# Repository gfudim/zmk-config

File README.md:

# zmk-config

## shallow miryoku zmk-config repo

A shallow "miryoku" layout implementation for my 36-Keys, diode-free/gpio-direct, custom keyboard.

### Parts

* PCB - 2 PCBs of K-36 split keyboard
* Controller - 2 Nice Nano micro controller
* Switches - 36 Kailh Choc switches of your choice
* Sockets - 36 Kailh hotswap sockets for choc switches
* Keycaps - 34 Choc keycaps, 2 Choc homing keycaps
* On\Off Switch - 2 PCM12SMTR micro toggle switch
* Reset Button - 2 B3U-1000P MD 2-foot tact switch 3*2.5*1.6 Micro button
* Battery - 2 301230 3.7v 110mah batteries(they fit under the nice nano mount)
* Connector - 2 PH 2.0 JST Connector Right Angle, Seat+Plug+Terminals
* Pads - Round Silicone Rubber Pads, 8x8x2.5mm (min height is 2.5mm because the hotswap sockets are 2mm in height)

### Details

* 5 columns, 3 rows, 3 thumb keys, 2 hands.
* Can be used on almost any split or non-split ergo or ortho keyboard.
* Includes all keys found on a US layout TKL keyboard, plus media keys and mouse emulation.
* Home row is the middle row, home thumb key is the middle thumb key.
* Maximum 1-u movement from home position for fingers and thumbs, and only along one axis (except for the inner index finger column which is deprioritised compared with the home columns).
* Dual-function modifiers on home row, mirrored on both hands.
* Dual-function layer change on thumbs.
* Layers are designed orthogonally with a single purpose per hand and are accessed by holding a thumb key on the opposite hand.
* All layers on the same hand are based on the same basic key arrangement.
* Holding layer change and modifiers on one hand combined with a single key press on the other hand can produce any combination of modifiers and single keys without any finger contortions.
* Single function mods are also defined on layers on the same hand as the layer change thumb key so layer change and mods can be held in any order or simultaneously without race conditions.
* As mods are only enabled on the opposite hand, auto-repeat is available on the home row on layers for use with cursor and mouse keys.
* Tap-hold auto-repeat is disabled to permit faster tap-hold switching on thumbs, but thumb tap keys are mirrored onto some layers for use with auto-repeat.  On other layers thumb keys are redefined with important functions for that layer.
* Auto Shift for numbers and symbols.
* Reset is available on sub layers on the same hand as the layer change thumb key.  Hold any thumb key and tap the top row pinkie column key on the same hand.

## Layers

### Base

Qwerty layout implemented

### Media

### Navigation

### Mouse

zmk doesn't support mouse movments on stable, so need's to be implemented once the feature is published.

### Symbol

### Number

### Function

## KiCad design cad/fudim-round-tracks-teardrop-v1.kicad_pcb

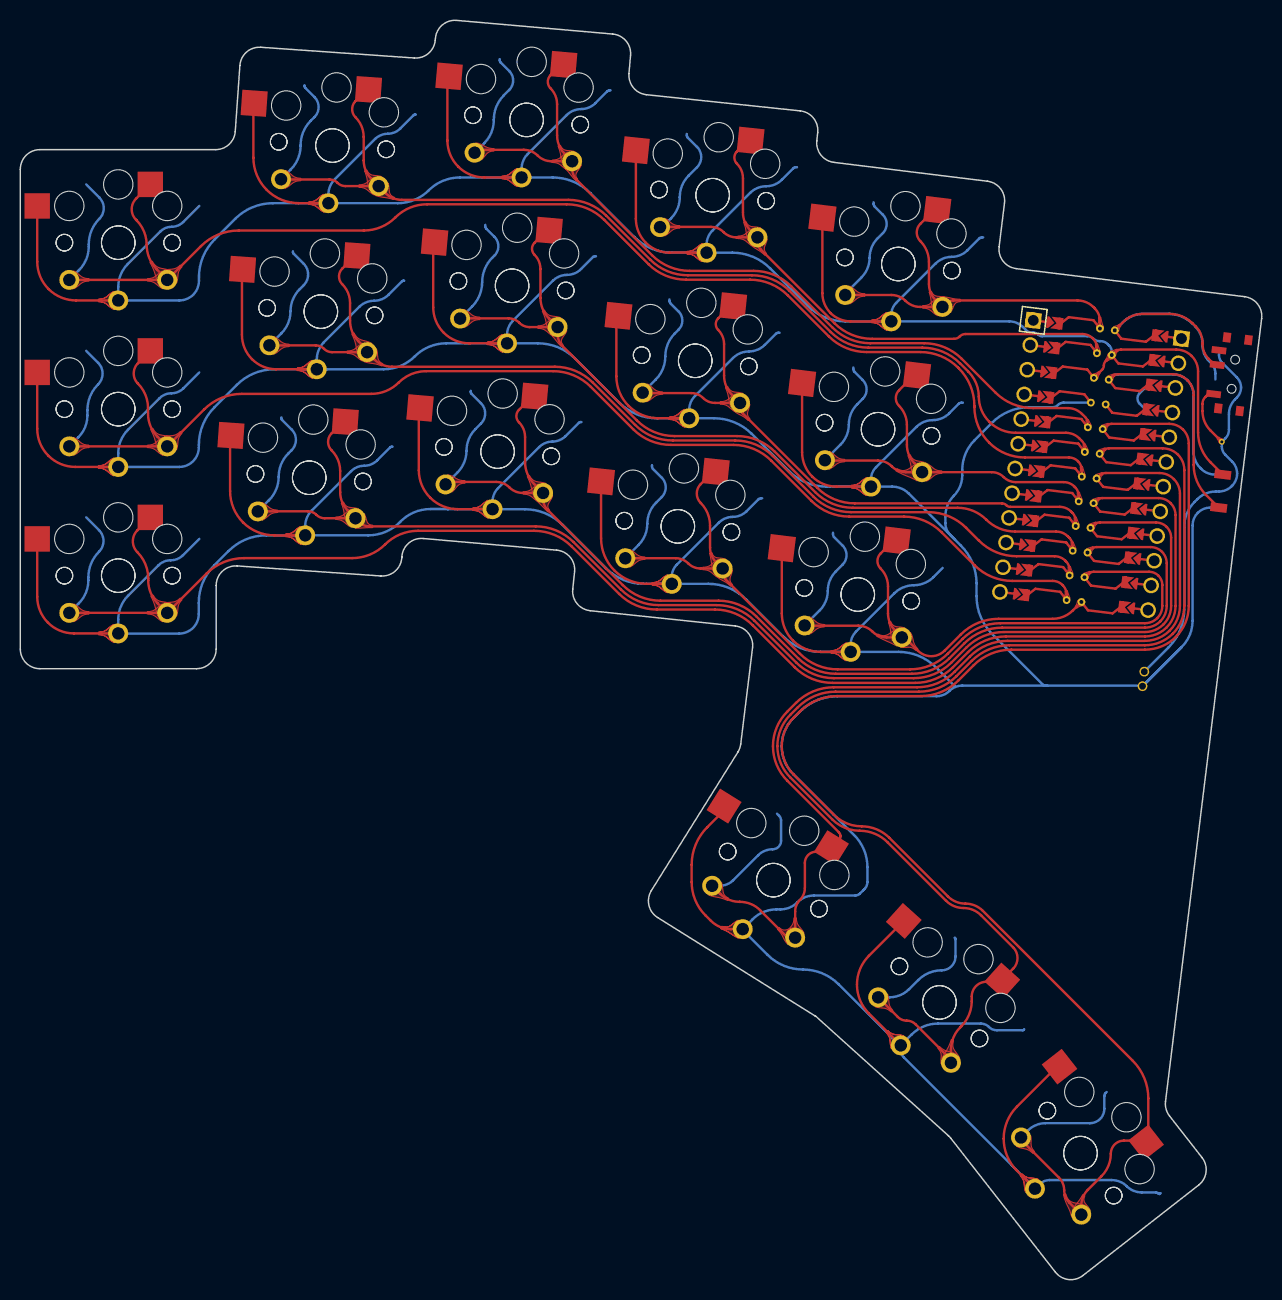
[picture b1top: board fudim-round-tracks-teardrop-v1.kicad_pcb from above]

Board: 2 copper layers, 126.8 x 128.6 mm, 37 parts (0 on the bottom side), 19 nets.

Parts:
MCU1: ProMicro
S1, S2, S3, S4, S5, S6, S7, S8, S9, S10, S11, S12, S13, S14, S15, S16, S17, S18, S19, S20, S21, S22, S23, S24, S25, S26, S27, S28, S29, S30, S31, S32, S33, S34, S35, S36: PG1350

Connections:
GND: MCU1.2, MCU1.21, MCU1.22, S1.2, S2.2, S3.2, S4.2, S5.2, S6.2, S7.2, S8.2, S9.2, S10.2, S11.2, S12.2, S13.2, S14.2, S15.2, S16.2, S17.2, S18.2, S19.2, S20.2, S21.2, S22.2, S23.2, S24.2, S25.2, S26.2, S27.2, S28.2, S29.2, S30.2, S31.2, S32.2, S33.2, S34.2, S35.2, S36.2
P0: MCU1.23, S23.1, S24.1
P1: MCU1.24, S29.1, S30.1
P2: MCU1.20, S17.1, S18.1
P3: MCU1.19, S11.1, S12.1
P4: MCU1.18, S5.1, S6.1
P5: MCU1.17, S27.1, S28.1
P6: MCU1.16, S21.1, S22.1
P7: MCU1.15, S15.1, S16.1
P8: MCU1.14, S9.1, S10.1
P9: MCU1.13, S3.1, S4.1
P10: MCU1.12, S25.1, S26.1
P14: MCU1.10, S13.1, S14.1
P15: MCU1.9, S7.1, S8.1
P16: MCU1.11, S19.1, S20.1
P18: MCU1.8, S1.1, S2.1
P19: MCU1.7, S31.1, S32.1
P20: MCU1.6, S33.1, S34.1
P21: MCU1.5, S35.1, S36.1

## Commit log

2022-12-31 intial setup
2022-12-31 fix promicro names
2023-01-01 west update
2023-01-01 build zmk
2023-01-01 inital readme
2023-03-25 home row tap timing
2023-03-29 cad and gerber files
2023-03-29 parts list
2023-03-29 image link fix
2023-04-08 SQT fix
2023-04-08 nav layer fix
2023-05-31 mouse layer attempt
2024-07-05 update defconfig to zmk main version
2024-07-05 mouse layer fix
2024-07-07 move around
2024-07-07 info.json added
2024-07-07 settings layer
2024-07-07 space fix
2024-07-07 move to none instead of trans
2024-07-07 urob homerow mods
2024-07-07 keypos defenitions
